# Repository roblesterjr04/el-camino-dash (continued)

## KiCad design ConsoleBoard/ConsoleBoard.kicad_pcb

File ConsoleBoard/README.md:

# Console board

The console's own board (CAN node `0x13`): a bare **ESP32-S3-WROOM-1-N8** (no dev board) with the parts it needs, a
female 2 × 8 socket the 100 × 33.5 mm **SSD1322 256 × 64 OLED** module plugs into, **Back** and **View** keys, four yellow LEDs (to match the yellow OLED), and top-entry
connectors for the **Select** and **Volume** encoders. One 4-wire cable goes to a DigiDash cable port.

For the 111.5 × 38.5 mm housing there is a variant with the same OLED and RetroSound knobs on RJ9 jacks instead of
keys and encoders: [`ConsoleBoardRS/`](../ConsoleBoardRS/).

| Files | |
| --- | --- |
| `ConsoleBoard.kicad_sch` / `.kicad_pcb` / `.kicad_pro` | The board: 100.0 × 50.0 mm, 4 layers, parts on both sides. KiCad 10 |
| `generate/` | Scripts that produced the files (`gen_sch.py`, `gen_pcb.py`, `drc.py`). Everything comes from stock KiCad libraries |

**Status:** superseded by [`ConsoleBoardRS/`](../ConsoleBoardRS/README.md) and left off the panel ([`Panel/README.md`](../Panel/README.md)). Ordered or built: not stated. The console firmware ([`firmware/esp32s3_console/`](../firmware/esp32s3_console/README.md)) is now written for ConsoleBoardRS.

## Mechanics

```
              100.0 mm
   +--o------------------------o--+  ---
   |                            :  |   the module (100 x 33.5) sits above the board on four standoffs (o)
   |        OLED module         :: |   its 2 x 8 pins plug into the socket J1 on the right edge (:)
   |                            :: |   33.5
   +--o------------------------o--+  ---   <- module's bottom edge
   |   *[ BACK ]*        *[ VIEW ]*  |  |   * = LED
   |     x=25            x=75      |  16.5   the board reaches 16.5 mm past the module (15 to 18 mm wanted)
   | J3 J4     USB      J5  J6     |  |     connectors along the bottom edge on the back (top entry, USB side entry)
   +-------------------------------+  ---
```

- **Keys:** PTS645 tact switches (click feel), centred at x = 25 and 75 mm and y = 37.5 mm, to sit behind the two
  facia openings (the facia is drawn at the board's 2:1 proportions: 100 × 50 mm). Four LEDs flank them, 9.5 mm either side of each key.
- **Front** (module side): J1, the four M2 holes, the two keys and the four LEDs with their resistors and MOSFET. Everything
  else is on the back, so the standoff height is set by the socket: J1 is a female socket (about 8.5 mm tall), so the module's pins plug into it and the standoffs should hold the module about that far above the board (check the length of the module's pins).
- **Back:** the ESP32 module (antenna on the top edge), USB-C, the CAN cable, both encoder connectors, the IR header,
  RESET / BOOT and all the passives. J3-J6 are top entry (vertical), so their cables plug straight into the back of the
  board inside the housing; only the USB-C opens past the bottom edge.
- **Module dimensions are parameters** at the top of `generate/gen_pcb.py`: the 100 × 33.5 mm outline and the four M2
  holes, 94 × 28 mm centre to centre (measured), centred on the module (3 mm in from the sides, 2.75 mm from the top
  and bottom). J1's centre line, between its two pin columns, is on the right-hand holes' line, shifted 0.5 mm toward
  the edge (`HDR_SHIFT`): columns at x = 96.23 and 98.77 mm. It is centred top to bottom between those two holes.

## Schematic blocks

| Block | Parts | Notes |
| --- | --- | --- |
| MCU | U1 ESP32-S3-WROOM-1-N8, 10k + 1 µF on EN, RESET (SW1), BOOT (SW2), 22 µF + 10 µF + 100 nF on 3V3 | No PSRAM, so GPIO 35-37 stay free. Native USB on GPIO 19 / 20 |
| Power | J3 pin 1 +5 V or USB VBUS, ORed by D1 / D2 (B5819W) into `+5V`; U3 AP7361C-33E (1 A, 0.36 V dropout, SOT-223) | The board runs from the cable in the car; USB-C is for programming and bench power. SOT-223 because U3 carries the ESP32, the OLED and the LEDs (up to about 0.6 W with the OLED all white) |
| CAN | U2 MCP2562-E/SN (VDD 5 V straight from J3, ahead of the OR diode, so it stays above its 4.5 V minimum; VIO 3.3 V, STBY low), 1k on RXD, D5 NUP2105L on the pair | Never terminated: the DigiDash board owns both 120 Ω |
| OLED | J1, 2 × 8, SPI on the ESP32's FSPI pins | See the pin table below |
| LEDs | D3, D4, D6, D7 yellow 0603 (about 590 nm, to match the OLED) (two per key), 100 Ω each from `+3V3` (about 13 mA each), Q1 2N7002 on the low side, 100k gate pull-down | Same 3.3 V rail as the OLED. GPIO 38 PWM (LEDC) dims all four |
| Keys, encoders | SW3 BACK, SW4 VIEW, J4 Select and J5 Volume (JST PH 4-pin top entry, B4B-PH-K, GND / A / B / SW), 10k pull-up + 10 nF on every line | The encoders are cabled to J4 / J5: the board has no encoder footprints |
| Extras | J6 IR receiver header (GND, 3.3 V, OUT), M2 holes H1-H4 tied to GND | The IR header is for the existing `encoder_controller` IR feature |

### Pins

| ESP32 GPIO | Signal | ESP32 GPIO | Signal |
| --- | --- | --- | --- |
| 12 / 11 / 10 | OLED SCK / MOSI / CS | 18 / 7 / 14 | Volume A / B / push |
| 9 / 8 | OLED D/C / RST | 21 | BACK |
| 5 / 6 | CAN TX / RX | 47 | VIEW |
| 15 / 16 / 17 | Select A / B / push | 38 | LED PWM |
| 19 / 20 | USB D- / D+ | 39 | IR in |

Strapping pins 0 (BOOT), 3, 45, 46 are not otherwise used.

### J1 (the OLED header) and the cable

The pin order below was **measured on the module** (a 2 × 8 header: odd pins in the row marked "1", even pins in the row
marked "2"), and the module works this way on the bench. Only the seven SPI pins are wired; the parallel-bus pins stay open,
as on the bench. Orientation, checked on the module: its even row (2 … 16) faces the board's outer (right) edge with pin 2
at the bottom (toward the keys), so module pin *n* sits on socket pad 17 − *n* (`SOCKET_NETS` in `generate/gen_sch.py`).

| Pin | Module | Board net | Pin | Module | Board net |
| --- | --- | --- | --- | --- | --- |
| 1 | GND | GND | 14 | D/C | OLED_DC |
| 2 | VCC | +3V3 | 15 | RES | OLED_RST |
| 4 | D0 (CLK) | OLED_SCK | 16 | CS | OLED_CS (100k to 3V3) |
| 5 | D1 (DIN) | OLED_MOSI | 3, 6-13 | NC, D2-D7, E/RD, R/W | open |

The module must be set for 4-wire SPI (its BS resistors), as it is in the firmware today.

J3 (cable to the DigiDash board, JST PH 4-pin top entry, B4B-PH-K): 1 +5 V, 2 CANH, 3 CANL, 4 GND (the cable-port order, see
`docs/hardware/accessory_ports.md`).

## Firmware notes

- CAN: TWAI on GPIO 5 (TX) / 6 (RX), node `0x13`, 500 kbit/s, as in `docs/protocols/can_bus.md`.
- OLED: the firmware's own SSD1322 driver (`firmware/esp32s3_console/src/oled_ssd1322.cpp`, NHD init table, whole
  16-grey frames turned 180°) on SPI with CS 10, DC 9, RST 8. The LEDs follow the same brightness through `ledcWrite` on GPIO 38.
- Keys and encoders are active-low with external pull-ups; use the internal pull-ups only as a fallback.
- Firmware: [`firmware/esp32s3_console/`](../firmware/esp32s3_console/) (soft keys, phone control, bench serial console).

## Regenerating

KiCad 10 with its stock libraries, numpy in KiCad's Python (`$KIPY -m pip install --user numpy`) and Freerouting
(Java 17 or newer, opens its window while it routes):

```bash
KIPY=/Applications/KiCad/KiCad.app/Contents/Frameworks/Python.framework/Versions/Current/bin/python3
python3 generate/gen_sch.py                                    # also writes generate/refs.json
JAVA=/opt/homebrew/opt/openjdk@17/bin/java $KIPY generate/gen_pcb.py --route freerouting.jar
python3 generate/drc.py
```

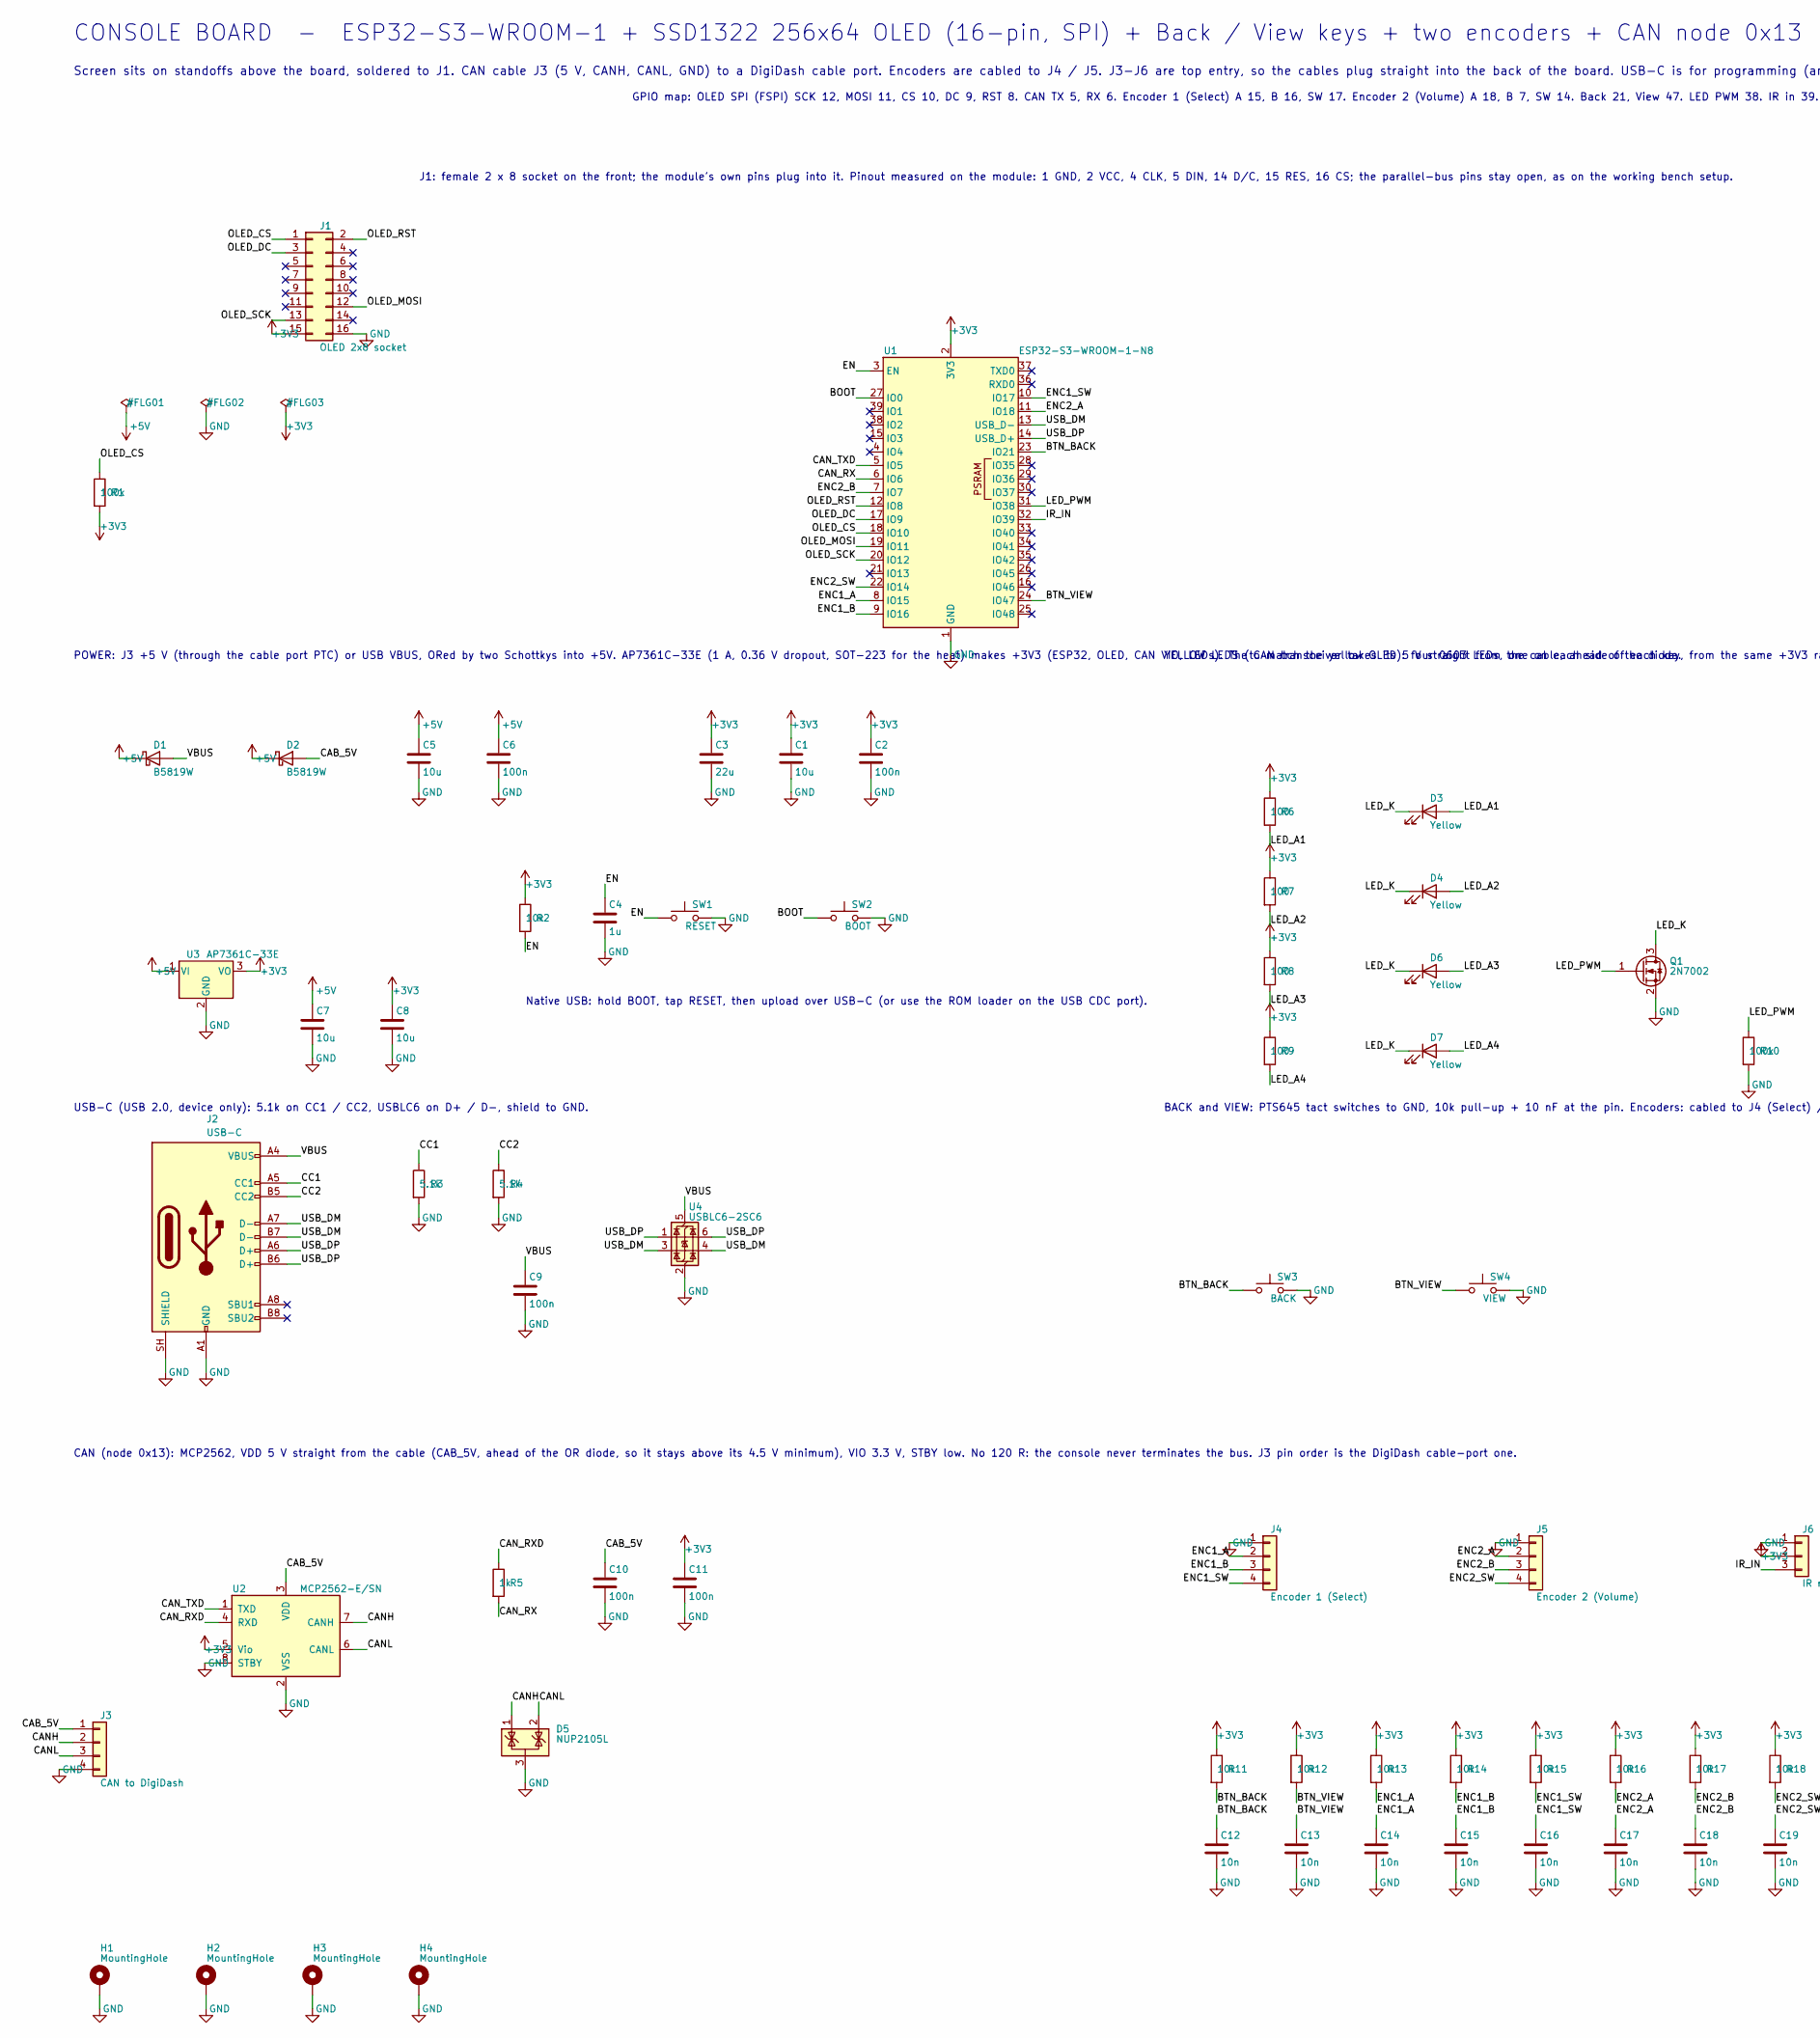
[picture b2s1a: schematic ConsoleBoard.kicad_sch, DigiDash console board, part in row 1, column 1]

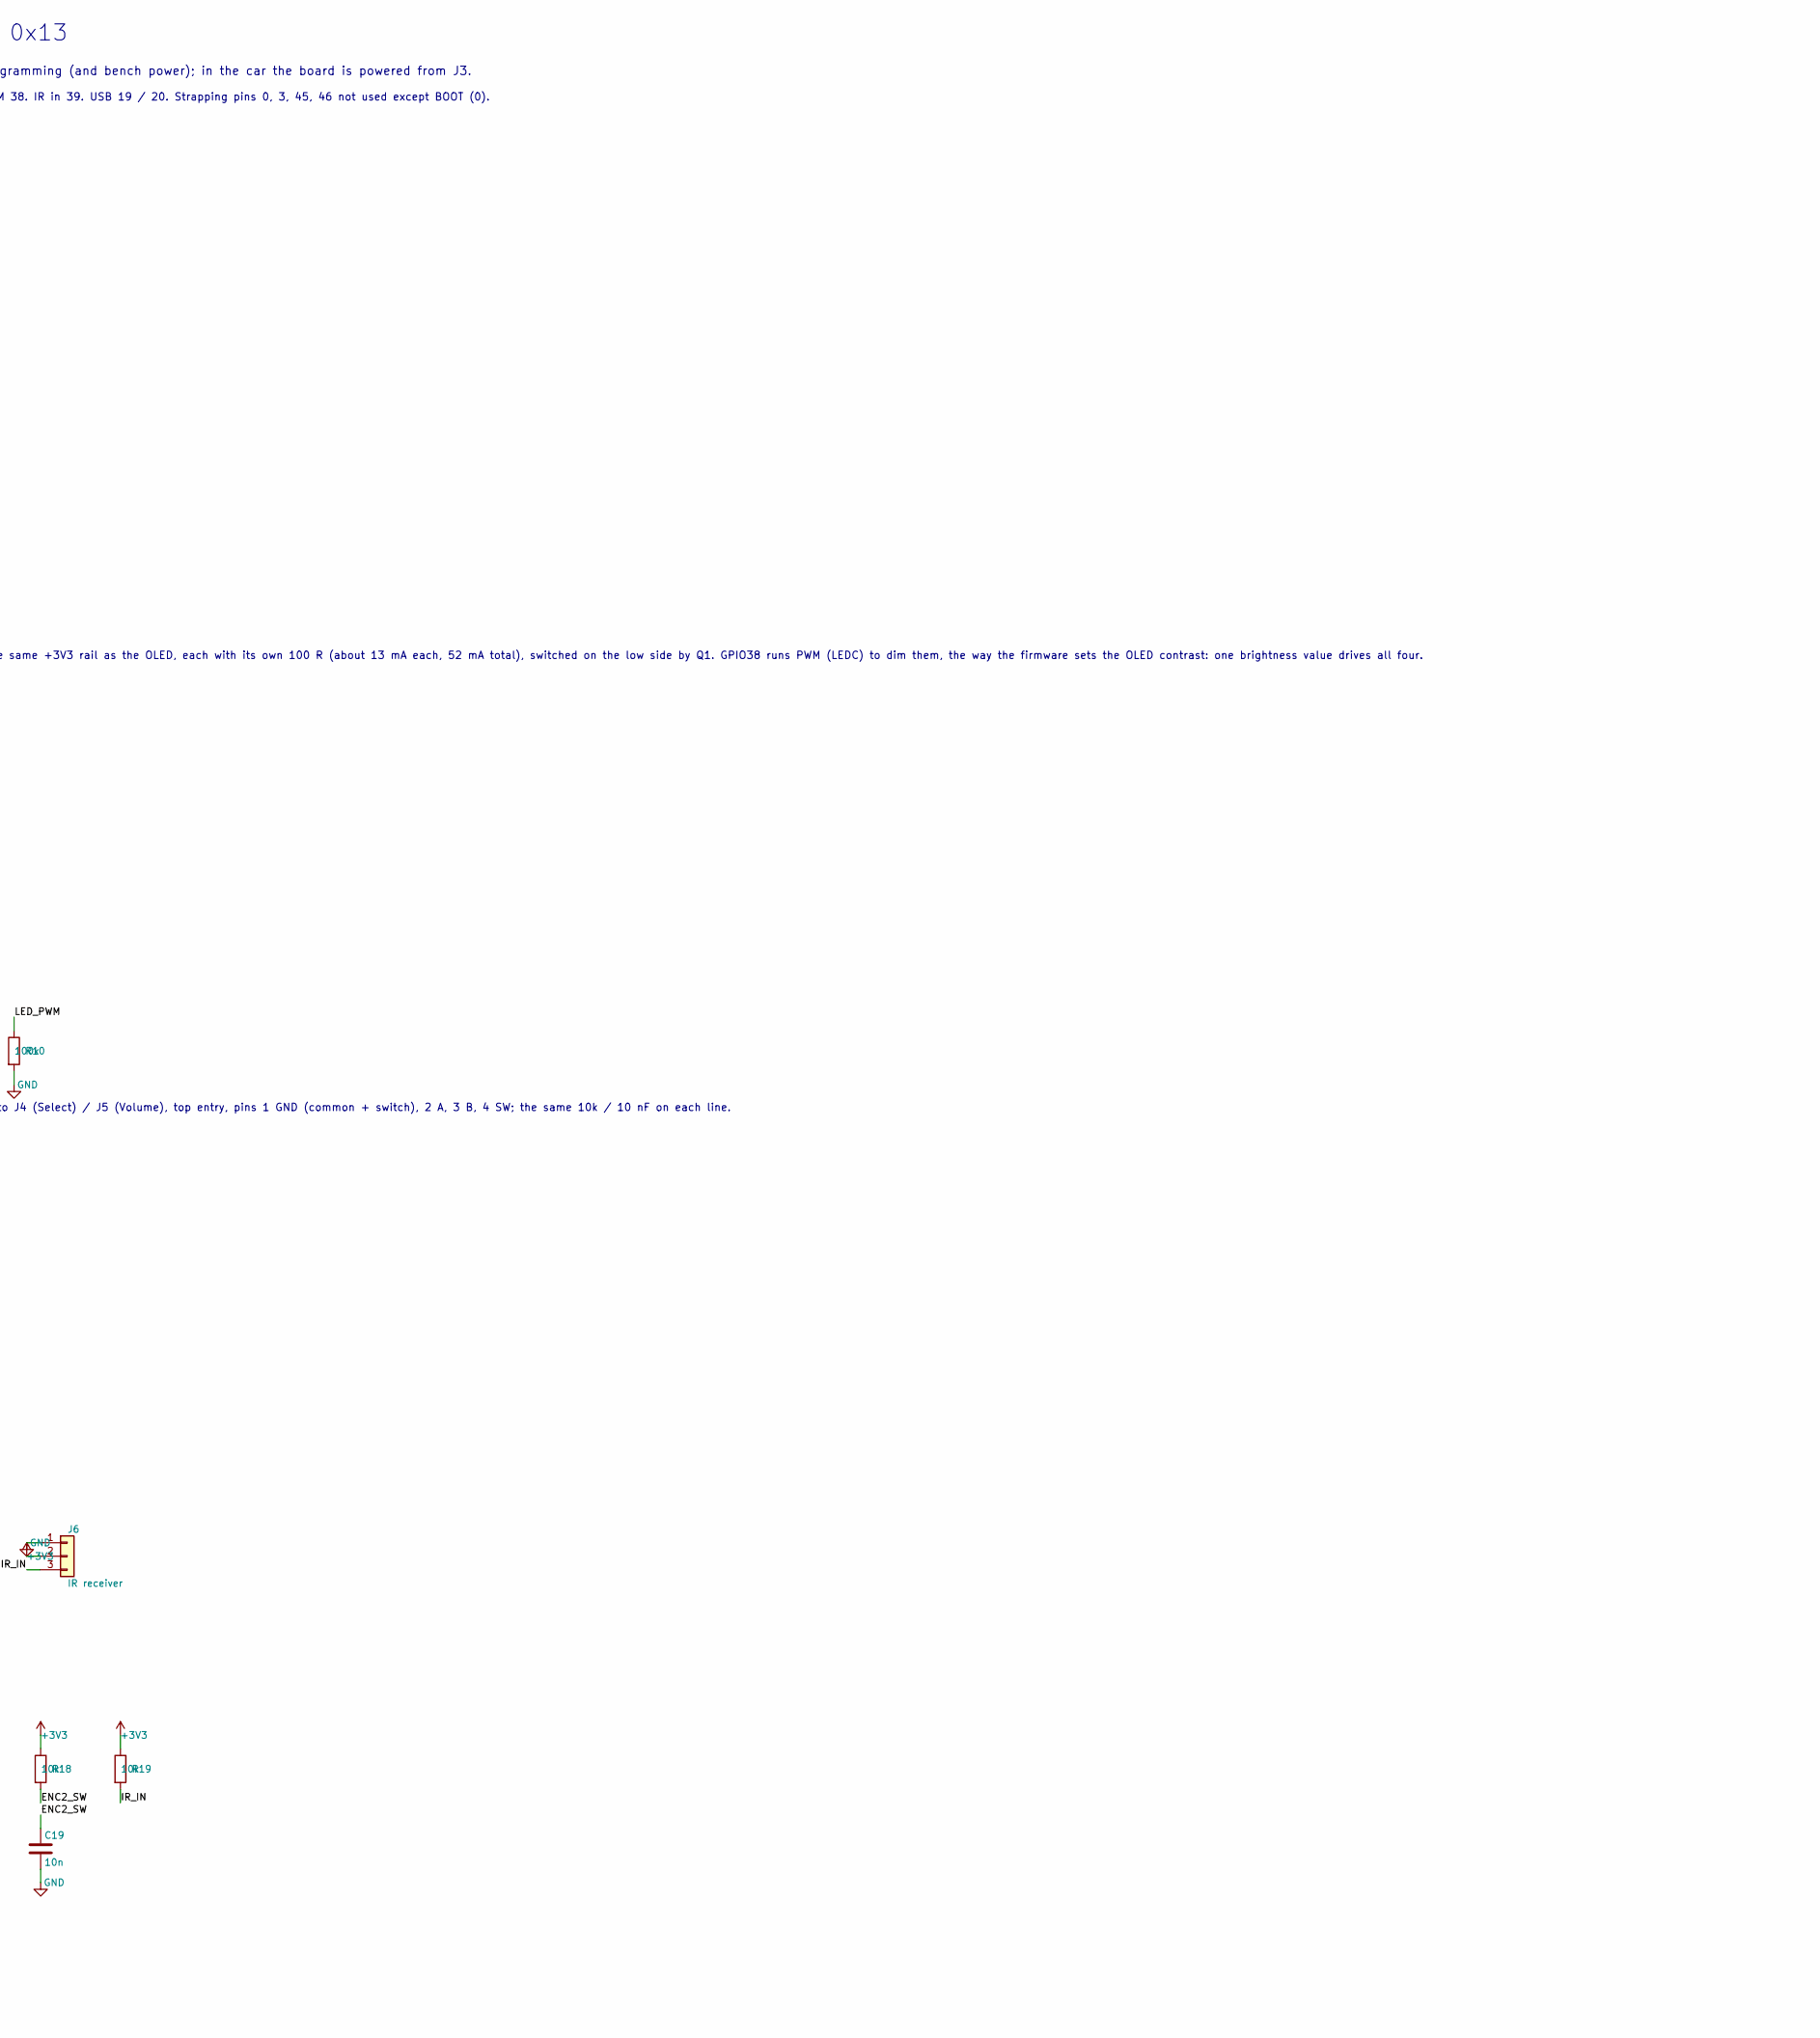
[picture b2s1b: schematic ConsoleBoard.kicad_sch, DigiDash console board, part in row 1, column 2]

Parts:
C1, C5, C7, C8: 10u; C_0805_2012Metric
C2, C6, C9, C10, C11: 100n; C_0603_1608Metric
C3: 22u; C_0805_2012Metric
C4: 1u; C_0603_1608Metric
C12, C13, C14, C15, C16, C17, C18, C19: 10n; C_0603_1608Metric
D1, D2: B5819W; D_SOD-123
D3, D4, D6, D7: Yellow; LED_0603_1608Metric
D5: NUP2105L; SOT-23
H1, H2, H3, H4: MountingHole; MountingHole_2.2mm_M2_Pad
J1: OLED 2x8 socket; PinSocket_2x08_P2.54mm_Vertical
J2: USB-C; USB_C_Receptacle_GCT_USB4105-xx-A_16P_TopMnt_Horizontal
J3: CAN to DigiDash; JST_PH_B4B-PH-K_1x04_P2.00mm_Vertical
J4: Encoder 1 (Select); JST_PH_B4B-PH-K_1x04_P2.00mm_Vertical
J5: Encoder 2 (Volume); JST_PH_B4B-PH-K_1x04_P2.00mm_Vertical
J6: IR receiver; PinHeader_1x03_P2.54mm_Vertical
Q1: 2N7002; SOT-23
R1, R10: 100k; R_0603_1608Metric
R2, R11, R12, R13, R14, R15, R16, R17, R18, R19: 10k; R_0603_1608Metric
R3, R4: 5.1k; R_0603_1608Metric
R5: 1k; R_0603_1608Metric
R6, R7, R8, R9: 100; R_0603_1608Metric
SW1: RESET; SW_SPST_PTS810
SW2: BOOT; SW_SPST_PTS810
SW3: BACK; SW_SPST_PTS645Sx43SMTR92
SW4: VIEW; SW_SPST_PTS645Sx43SMTR92
U1: ESP32-S3-WROOM-1-N8; ESP32-S3-WROOM-1
U2: MCP2562-E/SN; SOIC-8_3.9x4.9mm_P1.27mm
U3: AP7361C-33E; SOT-223-3_TabPin2
U4: USBLC6-2SC6; SOT-23-6

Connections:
+3V3: C1.1, C2.1, C3.1, C8.1, C11.1, J1.15, J6.2, R1.2, R2.1, R6.1, R7.1, R8.1, R9.1, R11.1, R12.1, R13.1, R14.1, R15.1, R16.1, R17.1, R18.1, R19.1, U1.2 (3V3), U2.5 (Vio), U3.3 (VO)
+5V: C5.1, C6.1, C7.1, D1.1 (K), D2.1 (K), U3.1 (VI)
/BOOT: SW2.1, U1.27 (IO0)
/BTN_BACK: C12.1, R11.2, SW3.1, U1.23 (IO21)
/BTN_VIEW: C13.1, R12.2, SW4.1, U1.24 (IO47)
/CAB_5V: C10.1, D2.2 (A), J3.1, U2.3 (VDD)
/CANH: D5.1 (K), J3.2, U2.7 (CANH)
/CANL: D5.2 (K), J3.3, U2.6 (CANL)
/CAN_RX: R5.2, U1.6 (IO6)
/CAN_RXD: R5.1, U2.4 (RXD)
/CAN_TXD: U1.5 (IO5), U2.1 (TXD)
/CC1: J2.A5 (CC1), R3.1
/CC2: J2.B5 (CC2), R4.1
/EN: C4.1, R2.2, SW1.1, U1.3 (EN)
/ENC1_A: C14.1, J4.2, R13.2, U1.8 (IO15)
/ENC1_B: C15.1, J4.3, R14.2, U1.9 (IO16)
/ENC1_SW: C16.1, J4.4, R15.2, U1.10 (IO17)
/ENC2_A: C17.1, J5.2, R16.2, U1.11 (IO18)
/ENC2_B: C18.1, J5.3, R17.2, U1.7 (IO7)
/ENC2_SW: C19.1, J5.4, R18.2, U1.22 (IO14)
/IR_IN: J6.3, R19.2, U1.32 (IO39)
/LED_A1: D3.2 (A), R6.2
/LED_A2: D4.2 (A), R7.2
/LED_A3: D6.2 (A), R8.2
/LED_A4: D7.2 (A), R9.2
/LED_K: D3.1 (K), D4.1 (K), D6.1 (K), D7.1 (K), Q1.3 (D)
/LED_PWM: Q1.1 (G), R10.1, U1.31 (IO38)
/OLED_CS: J1.1, R1.1, U1.18 (IO10)
/OLED_DC: J1.3, U1.17 (IO9)
/OLED_MOSI: J1.12, U1.19 (IO11)
/OLED_RST: J1.2, U1.12 (IO8)
/OLED_SCK: J1.13, U1.20 (IO12)
/USB_DM: J2.A7 (D-), J2.B7 (D-), U1.13 (USB_D-), U4.3 (I/O2), U4.4 (I/O2)
/USB_DP: J2.A6 (D+), J2.B6 (D+), U1.14 (USB_D+), U4.1 (I/O1), U4.6 (I/O1)
/VBUS: C9.1, D1.2 (A), J2.A4 (VBUS), J2.A9 (VBUS), J2.B4 (VBUS), J2.B9 (VBUS), U4.5 (VBUS)
GND: C1.2, C2.2, C3.2, C4.2, C5.2, C6.2, C7.2, C8.2, C9.2, C10.2, C11.2, C12.2, C13.2, C14.2, C15.2, C16.2, C17.2, C18.2, C19.2, D5.3 (A), H1.1, H2.1, H3.1, H4.1, J1.16, J2.A1 (GND), J2.A12 (GND), J2.B1 (GND), J2.B12 (GND), J2.SH (SHIELD), J3.4, J4.1, J5.1, J6.1, Q1.2 (S), R3.2, R4.2, R10.2, SW1.2, SW2.2, SW3.2, SW4.2, U1.1 (GND), U1.40 (GND), U1.41 (GND), U2.2 (VSS), U2.8 (STBY), U3.2 (GND), U4.2 (GND)

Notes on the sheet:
CONSOLE BOARD - ESP32-S3-WROOM-1 + SSD1322 256x64 OLED (16-pin, SPI) + Back / View keys + two encoders + CAN node 0x13
Screen sits on standoffs above the board, soldered to J1. CAN cable J3 (5 V, CANH, CANL, GND) to a DigiDash cable port. Encoders are cabled to J4 / J5. J3-J6 are top entry, so the cables plug straight into the back of the board. USB-C is for programming (and bench power); in the car the board is po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
J1: female 2 x 8 socket on the front; the module's own pins plug into it. Pinout measured on the module: 1 GND, 2 VCC, 4 CLK, 5 DIN, 14 D/C, 15 RES, 16 CS; the parallel-bus pins stay open, as on the working bench setup.
GPIO map: OLED SPI (FSPI) SCK 12, MOSI 11, CS 10, DC 9, RST 8. CAN TX 5, RX 6. Encoder 1 (Select) A 15, B 16, SW 17. Encoder 2 (Volume) A 18, B 7, SW 14. Back 21, View 47. LED PWM 38. IR in 39. USB 19 / 20. Strapping pins 0, 3, 45, 46 not used except BOOT (0).
Native USB: hold BOOT, tap RESET, then upload over USB-C (or use the ROM loader on the USB CDC port).
POWER: J3 +5 V (through the cable port PTC) or USB VBUS, ORed by two Schottkys into +5V. AP7361C-33E (1 A, 0.36 V dropout, SOT-223 for the heat) makes +3V3 (ESP32, OLED, CAN VIO, LEDs). The CAN transceiver takes its 5 V straight from the cable, ahead of the diode.
USB-C (USB 2.0, device only): 5.1k on CC1 / CC2, USBLC6 on D+ / D-, shield to GND.
CAN (node 0x13): MCP2562, VDD 5 V straight from the cable (CAB_5V, ahead of the OR diode, so it stays above its 4.5 V minimum), VIO 3.3 V, STBY low. No 120 R: the console never terminates the bus. J3 pin order is the DigiDash cable-port one.
YELLOW LEDS (to match the yellow OLED): four 0603 LEDs, one on each side of each key, from the same +3V3 rail as the OLED, each with its own 100 R (about 13 mA each, 52 mA total), switched on the low side by Q1. GPIO38 runs PWM (LEDC) to dim them, the way the firmware sets the OLED contrast: one br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
BACK and VIEW: PTS645 tact switches to GND, 10k pull-up + 10 nF at the pin. Encoders: cabled to J4 (Select) / J5 (Volume), top entry, pins 1 GND (common + switch), 2 A, 3 B, 4 SW; the same 10k / 10 nF on each line.

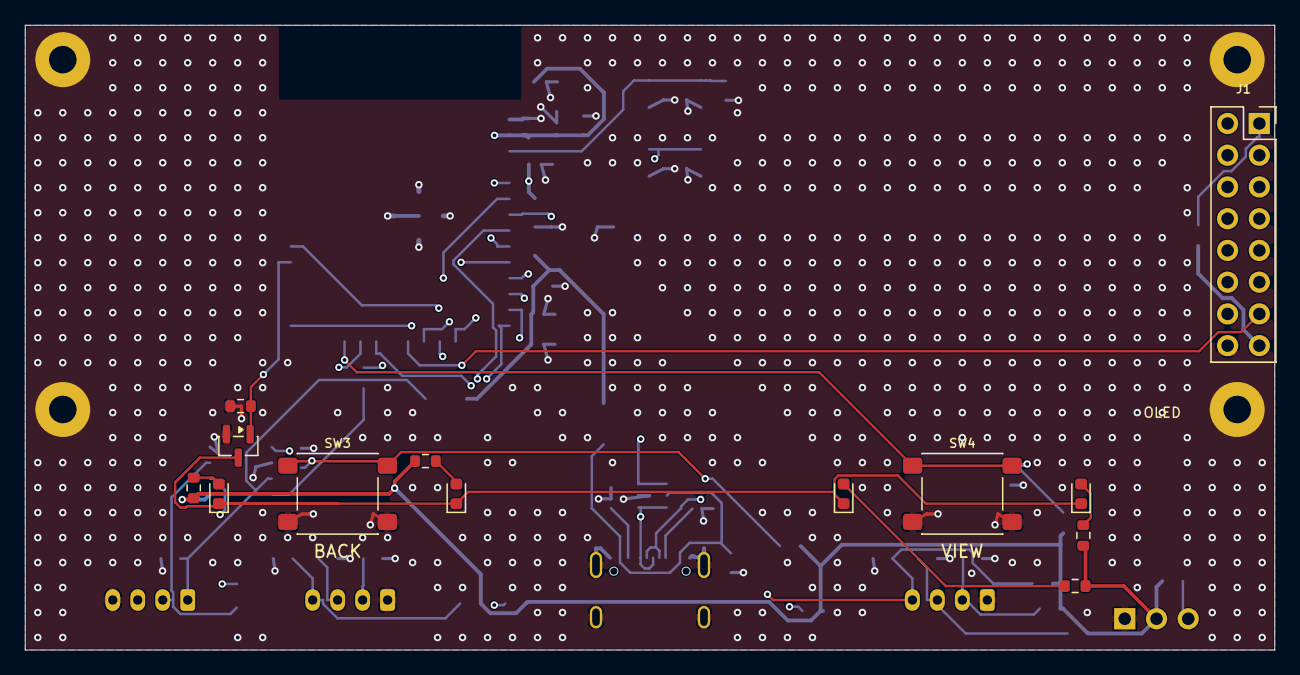
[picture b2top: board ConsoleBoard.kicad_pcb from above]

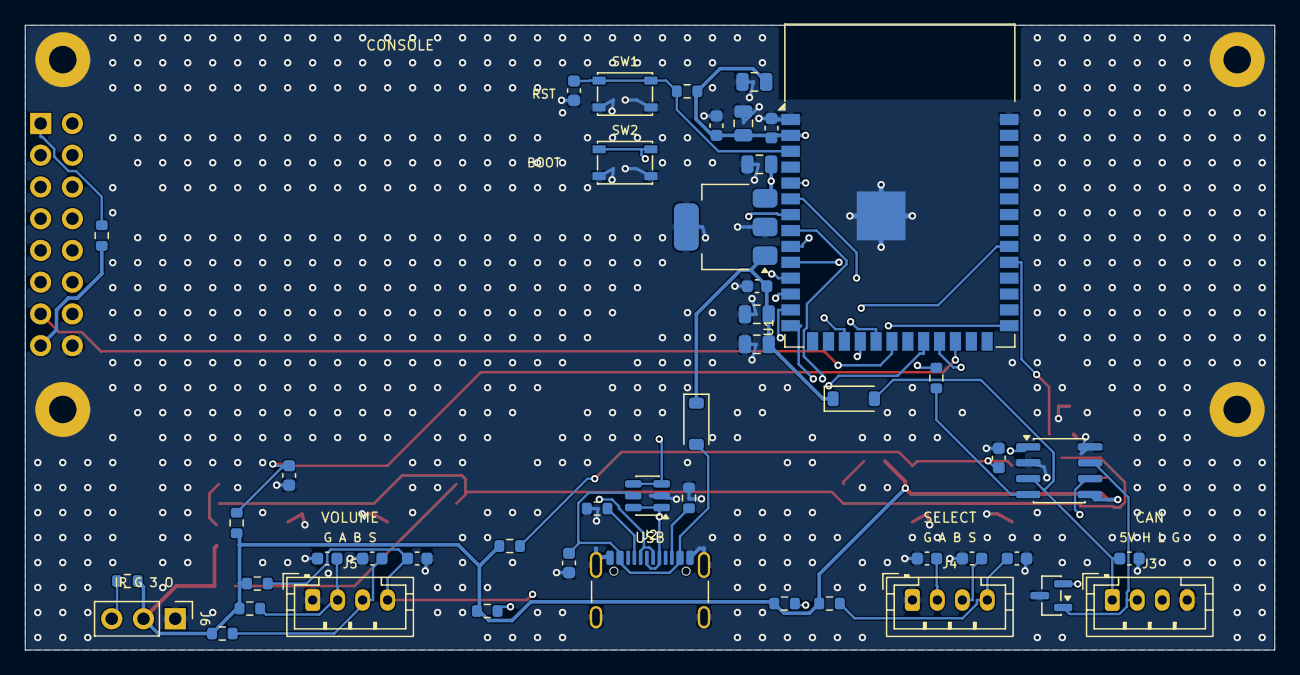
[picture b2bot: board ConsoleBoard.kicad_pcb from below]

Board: 4 copper layers, 100.0 x 50.0 mm, 64 parts (47 on the bottom side), 36 nets.

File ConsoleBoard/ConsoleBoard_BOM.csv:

Qty,Designators,Value,Description,Package / footprint,Manufacturer part (example),Notes
1,U1,ESP32-S3-WROOM-1-N8,"ESP32-S3 module, 8 MB flash, no PSRAM, PCB antenna",RF_Module:ESP32-S3-WROOM-1,Espressif ESP32-S3-WROOM-1-N8,"Antenna on the board edge, keep-out as placed"
1,U2,MCP2562-E/SN,"CAN FD transceiver, VDD 5 V (from the cable, ahead of the OR diode), VIO 3.3 V",SOIC-8,Microchip MCP2562-E/SN,
1,U3,AP7361C-33E,"LDO 3.3 V 1 A, 0.36 V dropout",SOT-223 (tab = GND),Diodes Inc AP7361C-33E-13,"SOT-223 for the heat: ESP32 + OLED + LEDs; pinout 1 IN, 2 GND, 3 OUT"
1,U4,USBLC6-2SC6,"USB ESD protection, 2 lines + VBUS",SOT-23-6,STMicroelectronics USBLC6-2SC6,
1,D5,NUP2105L,"CAN bus ESD clamp",SOT-23,onsemi NUP2105LT1G,
1,Q1,2N7002,"N-MOSFET, LED low-side switch",SOT-23,onsemi 2N7002LT1G,"Fine at 52 mA with a 3.3 V gate"
2,"D1, D2",B5819W,"Schottky 40 V 1 A (power OR: USB VBUS and cable 5 V)",SOD-123,any B5819W,
4,"D3, D4, D6, D7",Yellow,"LED, yellow (about 590 nm, to match the yellow OLED), 0603, Vf about 2.0 V",0603,"e.g. Kingbright APT1608SYCK (590 nm)","About 13 mA each through 100 R; buy all four from one lot so they match; check the colour against the OLED"
1,J1,2x8 female socket,"2.54 mm pin socket, 2 x 8, vertical (OLED module plugs in)",PinSocket_2x08_P2.54mm_Vertical,"any 2.54 mm 2x8 female, about 8.5 mm tall","Wired to the measured module pinout (1 GND, 2 VCC, 4 CLK, 5 DIN, 14 DC, 15 RES, 16 CS)"
1,J2,USB-C,"USB-C receptacle, USB 2.0, 16 pin, top mount",USB_C_Receptacle_GCT_USB4105-xx-A_16P_TopMnt_Horizontal,GCT USB4105-GF-A,
3,"J3, J4, J5",JST PH 4-pin,"JST PH 2.0 mm, 4 pin, top entry (vertical), through hole (J3 CAN cable, J4 Select encoder, J5 Volume encoder)",JST_PH_B4B-PH-K_1x04_P2.00mm_Vertical,JST B4B-PH-K-S(LF)(SN),"Mating housing PHR-4 + SPH-002T-P0.5S crimps (per cable)"
1,J6,1x3 header,"2.54 mm pin header, 1 x 3, vertical (optional IR receiver)",PinHeader_1x03_P2.54mm_Vertical,any,"Optional: fit only if the IR receiver is used"
2,"SW3, SW4",PTS645,"Tact switch 6 x 6 mm SMT (BACK, VIEW keys)",SW_SPST_PTS645Sx43SMTR92,C&K PTS645SM43SMTR92 LFS,"4.3 mm tall: check the height against the facia openings before ordering"
2,"SW1, SW2",PTS810,"Tact switch 4.2 x 3.2 mm SMT (RESET, BOOT)",SW_SPST_PTS810,C&K PTS810 SJM 250 SMTR LFS,
1,C3,22u,"Ceramic X5R 10 V",0805,any,ESP32 bulk
4,"C1, C5, C7, C8",10u,"Ceramic X5R 16 V (on +5V / +3V3)",0805,any,"16 V or 25 V rating keeps capacitance at 5 V (DC bias)"
1,C4,1u,"Ceramic X7R 16 V",0603,any,EN reset delay (with R2 10k)
5,"C2, C6, C9, C10, C11",100n,"Ceramic X7R 50 V",0603,any,
8,C12-C19,10n,"Ceramic X7R 50 V",0603,any,"Key / encoder debounce"
10,"R2, R11-R19",10k,"Resistor 1 % 1/10 W",0603,any,"R2 EN pull-up; R11-R19 key / encoder / IR pull-ups"
2,"R1, R10",100k,"Resistor 1 % 1/10 W",0603,any,"R1 OLED CS pull-up; R10 LED gate pull-down"
2,"R3, R4",5.1k,"Resistor 1 % 1/10 W",0603,any,USB-C CC1 / CC2 (device)
4,R6-R9,100,"Resistor 1 % 1/10 W",0603,any,LED current
1,R5,1k,"Resistor 1 % 1/10 W",0603,any,CAN RXD series
4,H1-H4,M2 hole,"Mounting hole 2.2 mm, plated, GND",MountingHole_2.2mm_M2_Pad,none (PCB feature),"Screen standoffs: M2, height to suit J1 plus the module's pins"

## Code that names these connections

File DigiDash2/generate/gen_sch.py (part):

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               '(TI TPS54560B typical application, 400 kHz), 3.3 V and 1.8 V LDOs, switched 12 V')
place(HDR[6], 'J7', 'Vehicle power', 'Connector_Molex:Molex_Micro-Fit_3.0_43650-0615_1x06_P3.00mm_Vertical',
      {'1': 'BATT_IN', '2': 'BATT_IN', '3': 'GND', '4': 'GND', '5': 'IGN_IN', '6': 'ILLUM_IN'},
      descr='Micro-Fit 3.0, 6 pin: 1-2 battery 12 V (constant), 3-4 ground, 5 ignition 12 V (key on), 6 illumination (dash lights on)')
place(PFET, 'Q2', 'SUD50P04-08', 'Package_TO_SOT_SMD:TO-252-2', {'1': 'Q2_G', '2': 'BATT_IN', '3': '12V_BATT'},
      descr='Reverse-polarity protection: P-FET, drain to the input, gate to ground (on when the battery is the right way round)')
r_('10k', 'Q2_G', 'GND', 'Q2 gate to ground')
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          descr='Board mounting hole, M3 (provisional: moves with the bezel)')

# ----------------------------------------------------------------------------- AUX 12 V (bay power)
cur[0] = Block('aux', 1, 'AUX 12 V: slot power from its own fused feed (pins 25-30 of every slot). Its return (AUX_GND) meets GND only at NT1.')
place(HDR[2], 'J13', 'AUX 12V in', 'Connector_Molex:Molex_Mini-Fit_Jr_5566-02A_2x01_P4.20mm_Vertical',
      {'1': 'AUX_IN', '2': 'AUX_GND'}, descr='Mini-Fit Jr 2 pin: 1 AUX 12 V (own 7.5 A fuse at the fuse box, switched), 2 ground')
place(FUSE, nid('F'), '5A mini blade', 'Fuse:Fuseholder_Blade_Mini_Keystone_3568', {'1': 'AUX_IN', '2': 'AUX_IN_F'},
      descr='Board fuse for all six slots together (mini blade, 5 A: AUX is sized for about 3 A, the LTE card)')
place(PFET, 'Q6', 'SUD50P04-08', 'Package_TO_SOT_SMD:TO-252-2', {'1': 'Q6_G', '2': 'AUX_IN_F', '3': 'AUX12'},
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r_('4.7k', '+3V3', 'CL_SDA', 'Cluster I2C pull-up (R15)')
r_('4.7k', '+3V3', 'CL_SCL', 'Cluster I2C pull-up (R16)')
# vehicle inputs to the screens
text(cur[0].x0 + 300, cur[0].y0 + 6, 'Vehicle inputs to the screens (as rev 1): illumination (J7 pin 6), reverse (J9 pin 1). J6: serial port (center UART2).', 1.6)
r_('10k', 'ILLUM_IN', 'Q1_B', 'Illumination base')
r_('10k', 'Q1_B', 'GND', 'Illumination base pull-down')
npn('Q1_B', 'GND', 'Illumination', 'Illumination: low = dim (center screen GPIO24, internal pull-up; not the side screens: USB D-)', ref='Q1')
c_('100n', 'Illumination', 'GND', 'Illumination filter')
place(HDR[4], 'J9', 'Backup Camera', FP_PH4, {'1': 'REV_IN', '2': 'CAM_12V', '3': None, '4': 'GND'},
      descr='1 reverse lamp 12 V, 2 camera power (switched, fused), 3 spare, 4 ground. Video: J11')
ptc('PTC 0.5A', 'SW12', 'CAM_12V', 'Camera 12 V')
r_('10k', 'REV_IN', 'Q3_B', 'Reverse trigger base')
r_('10k', 'Q3_B', 'GND', 'Reverse trigger base pull-down')
npn('Q3_B', 'GND', 'REV_TRIGGER', 'Reverse: low = in reverse (center GPIO25)', ref='Q3')
c_('100n', 'REV_TRIGGER', 'GND', 'Reverse filter')
# sensor-frame serial fan-out (optional): the sensor card's serial out (5 V) on a jumper wire to J27, one divider per screen
text(cur[0].x0 + 300, cur[0].y0 + 12, 'Sensor serial (optional, a jumper wire from the sensor card): J27 pin 1 (5 V TX) -> 10k / 20k divider per screen '
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    '18': 'V_D0', '17': 'V_D1', '16': 'V_D2', '15': 'V_D3', '14': 'V_D4', '13': 'V_D5', '12': 'V_D6', '11': 'V_D7',
    '9': 'VID_SCLK', '25': 'V_HS', '24': 'V_VS', '23': 'V_FID', '26': None, '27': 'VID_INTREQ',
    '21': 'CL_SCL', '22': 'CL_SDA'}, descr='Video decoder')
r_('22', 'VID_SCLK', 'V_PCLK', 'Pixel clock series (edge damping)')
place(XTAL, 'Y3', '14.31818MHz', FP_XTAL, {'1': 'VID_XTAL1', '2': 'GND', '3': 'VID_XTAL2', '4': 'GND'},
      descr='14.31818 MHz, +/-50 ppm, fundamental')   # YXC X32251431818MSB4SI: CL 20 pF, so 33p load caps
c_('33p', 'VID_XTAL1', 'GND', 'Y3 load (2 CL - Cstray)')
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# (0.3 V) for a reset without dumping the 2.2u straight into the GPIO
r_('10k', '+3V3', 'VID_RESETB', 'RESETB pull-up')
c_('2.2u', 'VID_RESETB', 'GND', 'RESETB delay (> 20 ms after the supplies)')
r_('1k', 'V_P17', 'VID_RESETB', 'RESETB from the center (GPIO52, J1 pin 36)')
for net in ('+1V8A', '+1V8A', '+1V8', '+3V3'):
    c_('100n', net, 'GND', 'U8 decoupling')
c_('10u', '+1V8', 'GND', 'U8 digital bulk')
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    ptc('PTC 0.2A', '12V_BATT', s + '_BATT', 'Slot %d constant 12 V (key-off functions)' % n, FP_PTC_S)
    r_(SLOT_ID[i], s + '_ID', 'GND', 'Slot %d ID: the card reads it against its own 10k pull-up to 3.3 V' % n)
text(cur[0].x0 + 300, cur[0].y0 + 6, 'WAKE: a card drives it high (about 3.3 V, through its own diode) to start or hold the 5 V rail with the key off '
     '(the sensor card holds it to finish after key-off). LAMP_LVL / REV_LVL: J7 pin 6 and J9 pin 1 scaled to 0-3.3 V.', 1.6)
r_('100k', 'WAKE', 'GND', 'WAKE idle low (cards only ever drive it high)')
place(BAT54S, nid('D'), 'BAT54S', FP_SOT23, {'1': 'WAKE', '2': None, '3': 'WAKE_K'},
      descr='Wake diode (pin 1 to pin 3): WAKE high lifts the buck EN; the second diode is unused')
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      descr='The only joint between the slots\' audio-bus ground and the logic ground')
# J6's 3.3 V through its own PTC, so a short on the serial cable cannot take the board's 3.3 V down (added last so the
# other parts keep their references)
ptc('PTC 0.1A', '+3V3', 'SER_3V3', 'Serial port 3.3 V (J6 pin 1)', FP_PTC_S)

# ----------------------------------------------------------------------------- write
for b in blocks:
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
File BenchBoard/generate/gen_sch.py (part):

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G('ctrl')
text(15, 185, 'WAKE: 100k pull-down (as DigiDash2); a card holding it high lights the WAKE LED (2N7002, so the LED loads nothing). '
     'LAMP / REV jumpers: fitted = dash lights on / in reverse. Each drives the slots\' level (3.3 V through 1k) and, through a '
     '2N7002, pulls the screen\'s pin low (GPIO24 illumination: low = dim; GPIO25 reverse trigger: low = reverse).', 1.4)
r_('100k', 'WAKE', 'GND', 30, 205, 'WAKE pull-down (as DigiDash2 R47)')
fet_('WAKE', 'WAKE_K', 45, 205, 'WAKE LED driver')
r_('1k', '+5V', 'WAKE_A', 60, 200, 'WAKE LED current')
place(LED, nid('D'), 'WAKE', FP_LED, 75, 200, {'2': 'WAKE_A', '1': 'WAKE_K'}, descr='WAKE LED: a card holds WAKE high')
hdr_(HDR1x2, 2, 'LAMP', 100, 205, {'1': '+3V3', '2': 'LAMP_SW'}, 'LAMP jumper: fitted = dash lights on')
r_('100k', 'LAMP_SW', 'GND', 115, 210, 'LAMP off without the jumper')
r_('1k', 'LAMP_SW', 'LAMP_LVL', 130, 200, 'LAMP level to the slots (pin 13)')
fet_('LAMP_SW', 'SCR_ILLUM', 145, 210, 'Screen illumination input (GPIO24, active low = dim)')
hdr_(HDR1x2, 2, 'REV', 170, 205, {'1': '+3V3', '2': 'REV_SW'}, 'REV jumper: fitted = in reverse')
r_('100k', 'REV_SW', 'GND', 185, 210, 'REV off without the jumper')
r_('1k', 'REV_SW', 'REV_LVL', 200, 200, 'REV level to the slots (pin 14)')
fet_('REV_SW', 'SCR_REV', 215, 210, 'Screen reverse trigger (GPIO25, active low)')

# --- CAN
G('can')
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     'up, facing away. Its pin numbers (Raspberry Pi order, on its silkscreen) meet this header\'s pads reversed: pad p = screen pin '
     '40 - p (odd) / 42 - p (even).\nScreen pins used (DigiDash2 J5 / J1 / J4 signals): 2 / 4 5 V; 6 9 14 20 25 30 34 39 GND; '
     '17 its 3V3 (role strap only); 18 GPIO4 role strap; 16 GPIO5 sensor serial in; 19 GPIO3 TX / 21 GPIO2 RX (serial port, '
     'firmware GPS_UART_TX / _RX); 24 GPIO36 CAN RX; 32 GPIO34 CAN TX; 27 GPIO24 illumination; 28 GPIO25 reverse; '
     '33 GPIO48 / 37 GPIO47 cluster I2C. Video pins: not used.', 1.4)
hdr_(HDR2x20, 20, 'Screen', 250, 320, scr,
     'Screen: 2x20 right-angle male header, 2.54 mm, at the board edge (pad p = screen pin 40 - p odd / 42 - p even)',
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
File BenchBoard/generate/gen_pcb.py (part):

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          'screen': ['J9', 'J10', 'J11', 'J13'], 'audio': ['J14', 'J15']}
GROUP_ORDER = ['power', 'can', 'screen', 'ctrl', 'slot', 'audio', 'misc']
POWER_NETS = {'+5V', '+3V3', '/VIN', '/VIN_RAW', '/SW12V', '/AUX_12V', '/AUX_GND', '/S1_5V', '/S2_5V', '/S1_12V', '/S2_12V',
              '/S1_3V3', '/S2_3V3', '/S1_BATT', '/S2_BATT', '/BUCK_SW'}   # local labels carry the sheet path
HIGH_CURRENT = ('/VIN_RAW', '/VIN', '+5V', '/BUCK_SW', '/SW12V', '/AUX_12V', '/AUX_GND')
KEEP_SILK = {'J1', 'J3', 'J4', 'J12', 'J14', 'J15'}   # J9: the SCREEN legend names it
HOLES = [(4.0, 4.0), (W - 4.0, 4.0), (4.0, H - 4.0), (W - 4.0, H - 4.0)]
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
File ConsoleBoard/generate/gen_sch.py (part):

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
# --- CAN
G('can')
text(15, 280, 'CAN (node 0x13): MCP2562, VDD 5 V straight from the cable (CAB_5V, ahead of the OR diode, so it stays above its 4.5 V minimum), VIO 3.3 V, STBY low. No 120 R: the console never terminates the bus. J3 pin order is the DigiDash cable-port one.', 1.4)
place(CAN, 'U2', 'MCP2562-E/SN', FP_SOIC, 55, 315, {'1': 'CAN_TXD', '2': 'GND', '3': 'CAB_5V', '4': 'CAN_RXD', '5': '+3V3',
                                                      '6': 'CANL', '7': 'CANH', '8': 'GND'})
r_('1k', 'CAN_RXD', 'CAN_RX', 95, 305, 'Series R on the receive line, as on the DigiDash board')
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c_('100n', '+3V3', 'GND', 130, 305)
place(NUP, 'D5', 'NUP2105L', FP_SOT23, 100, 335, {'1': 'CANH', '2': 'CANL', '3': 'GND'}, descr='CAN ESD clamp at the cable')
place(HDR4, 'J3', 'CAN to DigiDash', FP_PH, 20, 335, {'1': 'CAB_5V', '2': 'CANH', '3': 'CANL', '4': 'GND'},
      descr='JST PH 4-pin top entry: 1 +5 V, 2 CANH, 3 CANL, 4 GND (cable port order, docs/hardware/accessory_ports.md)')

# --- backlight LEDs
G('led')
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
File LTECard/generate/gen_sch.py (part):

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    'IO40': 'LTE_RTS',      # UART1 RTS -> core board RTS (module input)
    'IO39': 'LTE_CTS',      # UART1 CTS <- core board CTS (module output)
    'IO38': 'LTE_DTR',      # DTR, held low (awake)
    'IO21': 'LTE_RI',       # RI in (can wake the ESP32: RTC-capable is not needed, GPIO wake works from light sleep)
    'IO11': 'PEN_IO',       # PEN out (through 1k), 100k pull-down: LTE off until the firmware raises it
    'IO12': 'RST_IO',       # RST out (through 1k)
    'IO13': 'STA_IO',       # STA in (through 1k)
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G('buck')
text(300, 220, 'LTE 5 V: TPS54560B from AUX 12 V (slot pins 25-27), the main board\'s 5 V circuit (TI datasheet typical application,\n'
     '400 kHz, 5.0 V) with a smaller inductor (6.8 uH, 7 x 7 mm). Load: the core board, about 2 A in LTE transmit bursts.\n'
     'All of its grounds are AUX_GND (slot pins 28-30), the AUX return: the LTE current never flows in the logic ground.\n'
     'EN from AUX through 442k / 90.9k: starts above about 6.5 V, clamped by a 5.1 V zener (EN abs. max 8.4 V).', 1.4)
for k in range(3):
    c_('2.2u 100V', 'AUX12', 'AUX_GND', 300 + 15 * k, 255, d='Buck input, at VIN (C1-C3 in the TI example)')
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G('lte')
text(300, 40, 'LTE CORE BOARD (SIMCom A7670, Cat-1) on two female sockets, 2.54 mm, 8.5 mm tall: J2 1 x 12 (row A, left), J3 1 x 11 (row B, right).\n'
     'PIN ORDER AND ROW SPACING ARE PROVISIONAL (from the vendor listings): measure the board, then edit CORE_ROW_A / CORE_ROW_B in gen_sch.py\n'
     'and the CORE_* constants in gen_pcb.py. VIN (5-16 V) <- LTE_5V from the card\'s buck, + 470 uF bulk at the socket. VTTL = 3.3 V\n'
     '(the board\'s TXS0108E reference). GND = AUX_GND. VBTA, VEXT, 5V, IO0, IO1, SR, SD, SC not connected.', 1.4)
place(HDR[12], 'J2', 'LTE core row A', 'Connector_PinSocket_2.54mm:PinSocket_1x12_P2.54mm_Vertical', 320, 110,
      {str(k + 1): CORE_NETS[n] for k, n in enumerate(CORE_ROW_A)},
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r_('1k', 'RST_IO', 'LTE_RST', 440, 150, 'RST series')
r_('1k', 'LTE_STA', 'STA_IO', 460, 150, 'STA series (input)')
r_('1k', 'LTE_NET', 'NET_IO', 480, 150, 'NET series (input)')
text(410, 185, 'AUX PRESENT: LTE_5V -> 22k / 33k -> GPIO5 (3.0 V while the buck runs). Tells "no AUX power" from "no LTE signal".', 1.4)
r_('22k', 'LTE_5V', 'AUX_SENSE', 420, 200, 'AUX present divider top')
r_('33k', 'AUX_SENSE', 'GND', 440, 200, 'AUX present divider bottom')
c_('100n', 'AUX_SENSE', 'GND', 460, 200, d='AUX present filter')
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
